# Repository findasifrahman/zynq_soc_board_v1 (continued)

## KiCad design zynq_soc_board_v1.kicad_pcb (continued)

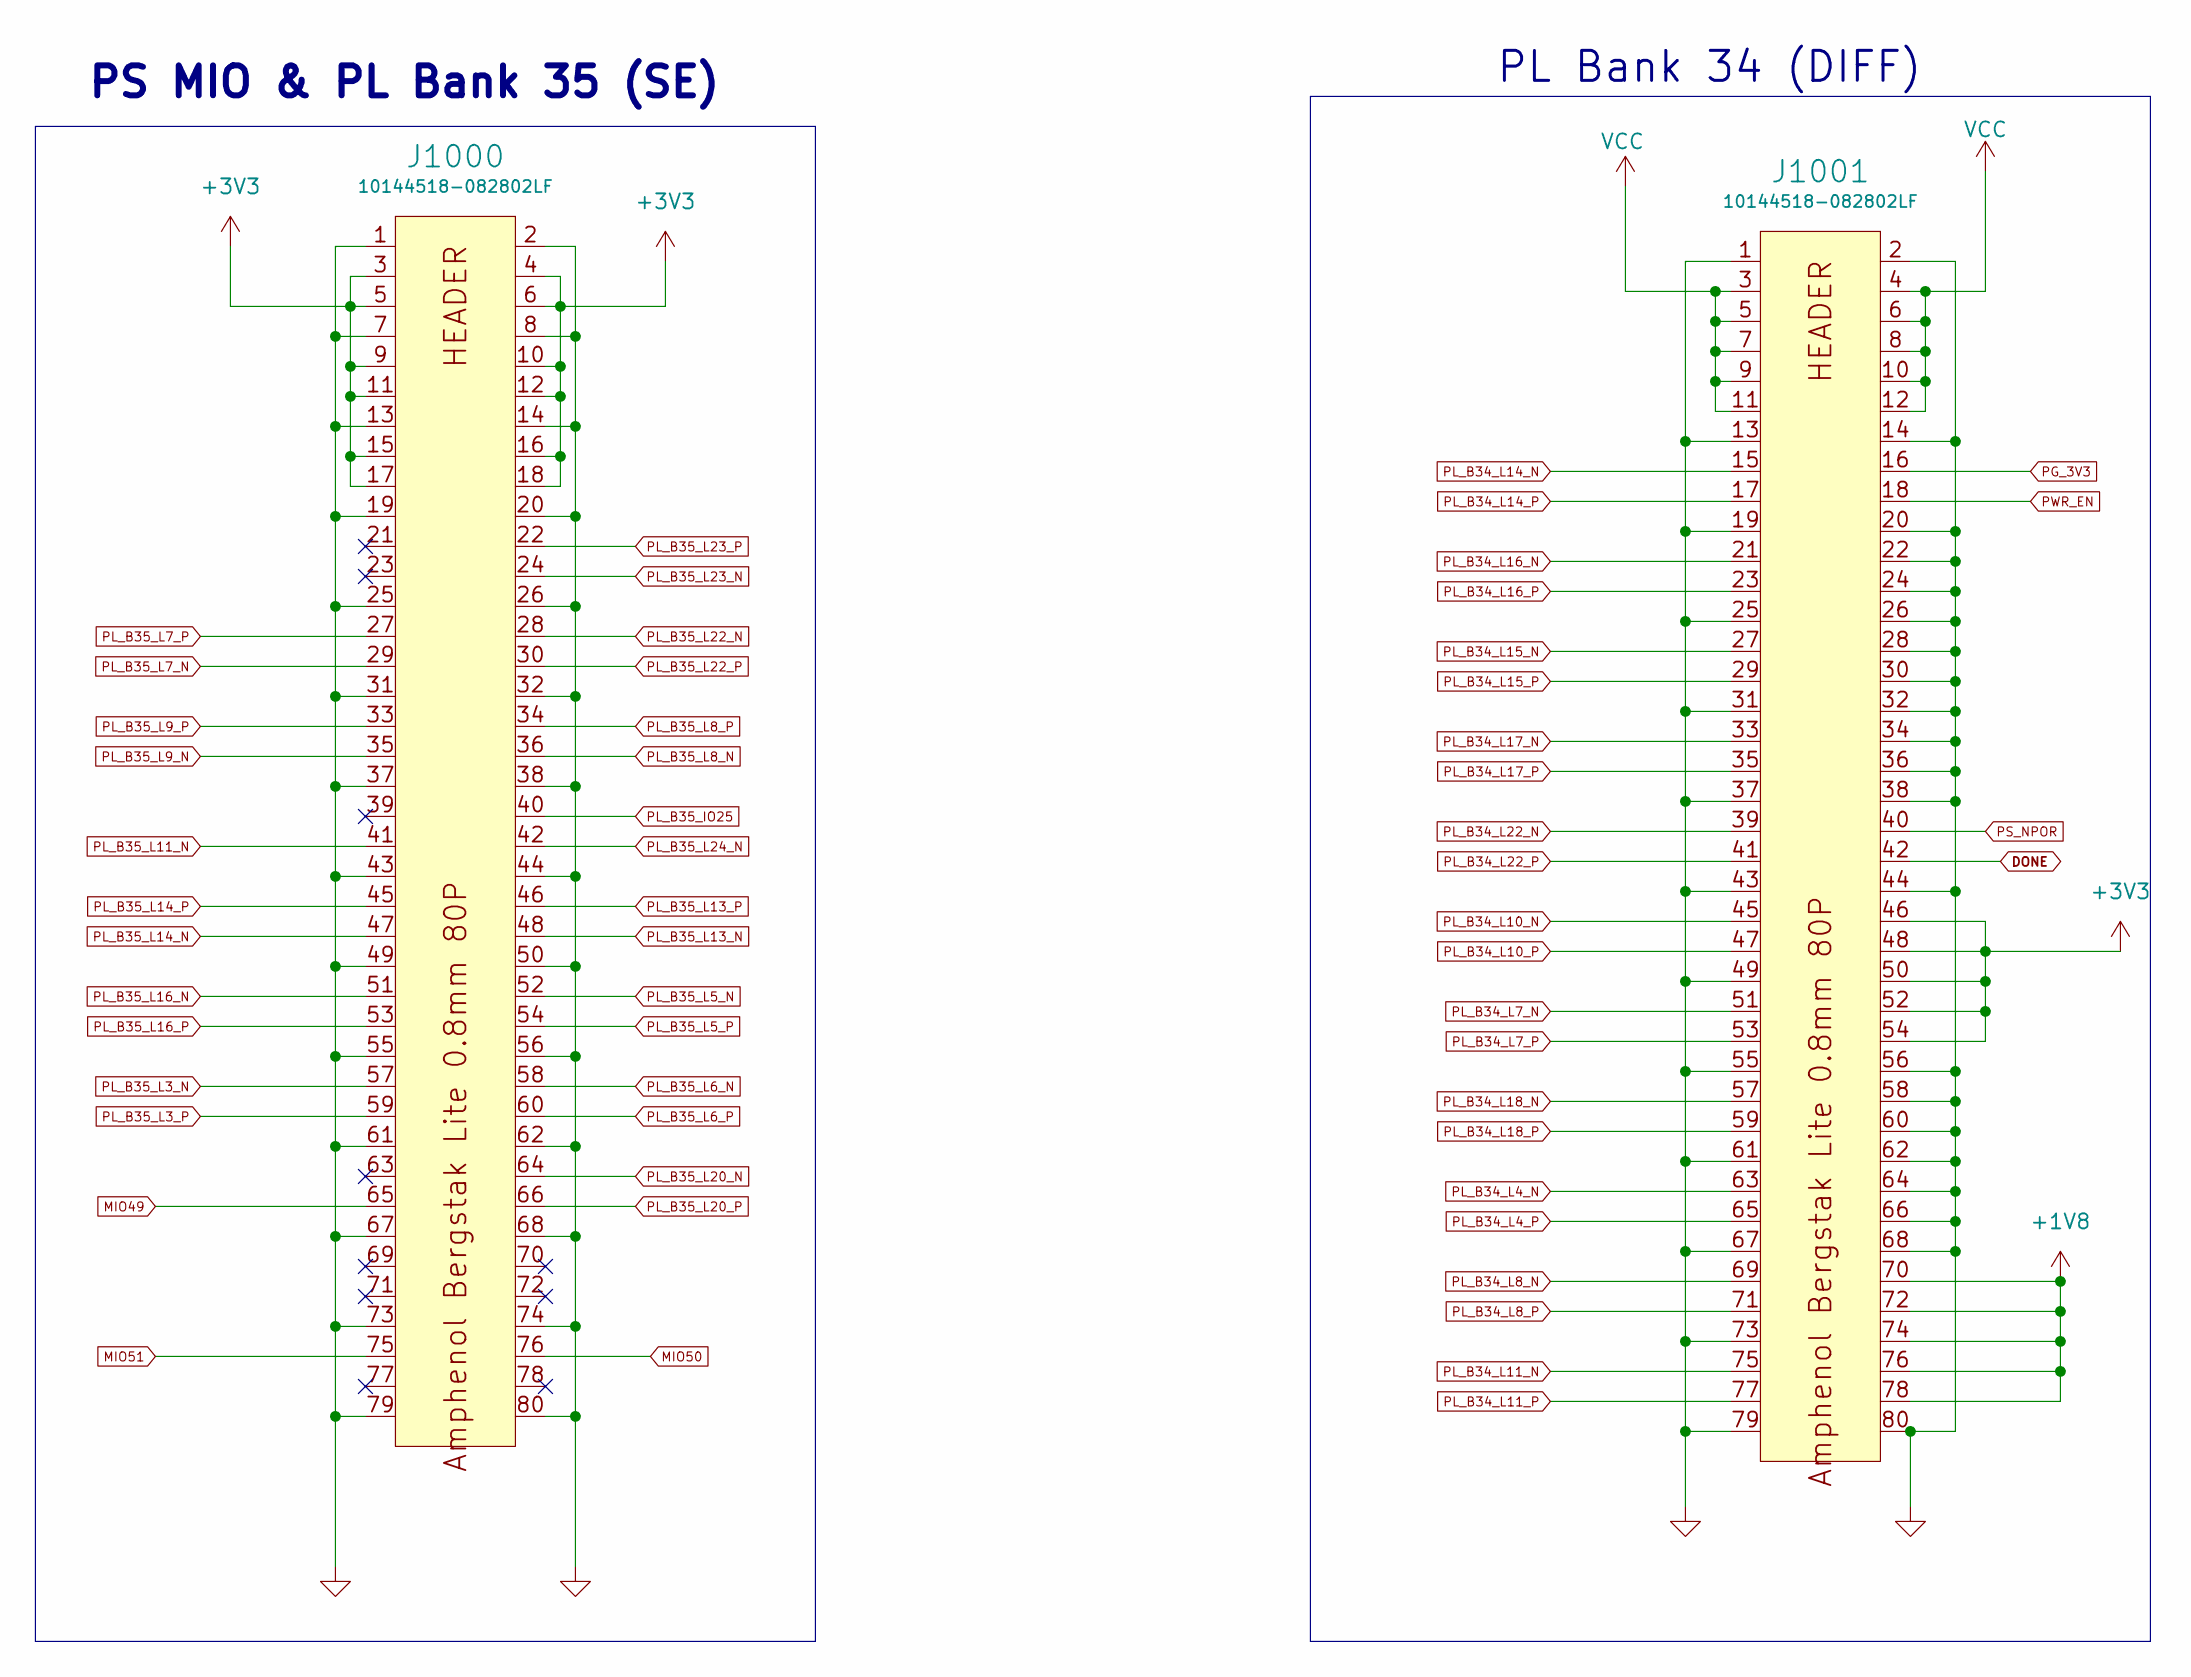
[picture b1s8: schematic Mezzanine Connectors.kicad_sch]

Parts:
J1000, J1001: 10144518-082802LF; Manufacturer Part Number 10144518-082802LF; LCSC C3653168

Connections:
+1V8: J1001.70, J1001.72, J1001.74, J1001.76, J1001.78; also elsewhere on the board
+3V3: J1000.3, J1000.4, J1000.5, J1000.6, J1000.9, J1000.10, J1000.11, J1000.12, J1000.15, J1000.16, J1000.17, J1000.18, J1001.46, J1001.48, J1001.50, J1001.52, J1001.54; also elsewhere on the board
DONE: J1001.42; also elsewhere on the board
GND: J1000.1, J1000.2, J1000.7, J1000.8, J1000.13, J1000.14, J1000.19, J1000.20, J1000.25, J1000.26, J1000.31, J1000.32, J1000.37, J1000.38, J1000.43, J1000.44, J1000.49, J1000.50, J1000.55, J1000.56, J1000.61, J1000.62, J1000.67, J1000.68, J1000.73, J1000.74, J1000.79, J1000.80, J1001.1, J1001.2, J1001.13, J1001.14, J1001.19, J1001.20, J1001.22, J1001.24, J1001.25, J1001.26, J1001.28, J1001.30, J1001.31, J1001.32, J1001.34, J1001.36, J1001.37, J1001.38, J1001.43, J1001.44, J1001.49, J1001.55, J1001.56, J1001.58, J1001.60, J1001.61, J1001.62, J1001.64, J1001.66, J1001.67, J1001.68, J1001.73, J1001.79, J1001.80; also elsewhere on the board
MIO49: J1000.65; also elsewhere on the board
MIO50: J1000.76; also elsewhere on the board
MIO51: J1000.75; also elsewhere on the board
PG_3V3: J1001.16; also elsewhere on the board
PL_B34_L4_N: J1001.63; also elsewhere on the board
PL_B34_L4_P: J1001.65; also elsewhere on the board
PL_B34_L7_N: J1001.51; also elsewhere on the board
PL_B34_L7_P: J1001.53; also elsewhere on the board
PL_B34_L8_N: J1001.69; also elsewhere on the board
PL_B34_L8_P: J1001.71; also elsewhere on the board
PL_B34_L10_N: J1001.45; also elsewhere on the board
PL_B34_L10_P: J1001.47; also elsewhere on the board
PL_B34_L11_N: J1001.75; also elsewhere on the board
PL_B34_L11_P: J1001.77; also elsewhere on the board
PL_B34_L14_N: J1001.15; also elsewhere on the board
PL_B34_L14_P: J1001.17; also elsewhere on the board
PL_B34_L15_N: J1001.27; also elsewhere on the board
PL_B34_L15_P: J1001.29; also elsewhere on the board
PL_B34_L16_N: J1001.21; also elsewhere on the board
PL_B34_L16_P: J1001.23; also elsewhere on the board
PL_B34_L17_N: J1001.33; also elsewhere on the board
PL_B34_L17_P: J1001.35; also elsewhere on the board
PL_B34_L18_N: J1001.57; also elsewhere on the board
PL_B34_L18_P: J1001.59; also elsewhere on the board
PL_B34_L22_N: J1001.39; also elsewhere on the board
PL_B34_L22_P: J1001.41; also elsewhere on the board
PL_B35_IO25: J1000.40; also elsewhere on the board
PL_B35_L3_N: J1000.57; also elsewhere on the board
PL_B35_L3_P: J1000.59; also elsewhere on the board
PL_B35_L5_N: J1000.52; also elsewhere on the board
PL_B35_L5_P: J1000.54; also elsewhere on the board
PL_B35_L6_N: J1000.58; also elsewhere on the board
PL_B35_L6_P: J1000.60; also elsewhere on the board
PL_B35_L7_N: J1000.29; also elsewhere on the board
PL_B35_L7_P: J1000.27; also elsewhere on the board
PL_B35_L8_N: J1000.36; also elsewhere on the board
PL_B35_L8_P: J1000.34; also elsewhere on the board
PL_B35_L9_N: J1000.35; also elsewhere on the board
PL_B35_L9_P: J1000.33; also elsewhere on the board
PL_B35_L11_N: J1000.41; also elsewhere on the board
PL_B35_L13_N: J1000.48; also elsewhere on the board
PL_B35_L13_P: J1000.46; also elsewhere on the board
PL_B35_L14_N: J1000.47; also elsewhere on the board
PL_B35_L14_P: J1000.45; also elsewhere on the board
PL_B35_L16_N: J1000.51; also elsewhere on the board
PL_B35_L16_P: J1000.53; also elsewhere on the board
PL_B35_L20_N: J1000.64; also elsewhere on the board
PL_B35_L20_P: J1000.66; also elsewhere on the board
PL_B35_L22_N: J1000.28; also elsewhere on the board
PL_B35_L22_P: J1000.30; also elsewhere on the board
PL_B35_L23_N: J1000.24; also elsewhere on the board
PL_B35_L23_P: J1000.22; also elsewhere on the board
PL_B35_L24_N: J1000.42; also elsewhere on the board
PS_NPOR: J1001.40; also elsewhere on the board
PWR_EN: J1001.18; also elsewhere on the board
VCC: J1001.3, J1001.4, J1001.5, J1001.6, J1001.7, J1001.8, J1001.9, J1001.10, J1001.11, J1001.12; also elsewhere on the board

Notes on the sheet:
PS MIO & PL Bank 35 (SE)
PL Bank 34 (DIFF)

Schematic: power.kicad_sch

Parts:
C100, C103, C104, C107, C108, C109, C112, C113, C114, C117, C118, C119, C122, C123, C124, C127: 22u; C0805; Manufacturer Part Number CL21A226MAQNNNE; LCSC C45783
C101, C102, C105, C110, C115: 100n; C_0402_1005Metric; Manufacturer Part Number CL05B104KO5NNNC; LCSC C1525
C106, C111, C116, C121: 22p; C_0402_1005Metric; Manufacturer Part Number 0402CG220J500NT; LCSC C1555
C120, C125, C126, C128, C129: 4u7; C_0402_1005Metric; Manufacturer Part Number CL05A475MP5NRNC; LCSC C23733
C130: 1nf,250v; C2211; Manufacturer Part Number GA352QR7GF102KW01L; LCSC C91599
D100: PMEG1030EJ; D_SOD-323F; LCSC C133633
D101: RED; LED_0402_RED; Manufacturer Part Number NCD0402R1; LCSC C130719
H1, H2, H3, H4: MountingHole; MountingHole_3.2mm_M3
J100: CON-SOCJ-2155; DC-IN-TH_DC005-T20; Manufacturer Part Number CON-SOCJ-2155; LCSC C111567
L100, L101, L102, L103: 2uh2; IND-SMD_L4.4-W4.1; Manufacturer Part Number SRP0415-2R2K; LCSC C1858073
Q100: T2N7002AK; SOT-23; Manufacturer Part Number T2N7002AK,LM; LCSC C516175
R100, R126: 100k; R_0402_1005Metric; Manufacturer Part Number 0402WGF1003TCE; LCSC C25741
R101, R103, R105, R108, R110, R113, R115, R118, R120, R123, R125: 12K; R_0402_1005Metric; Manufacturer Part Number 0402WGF1202TCE; LCSC C25752
R102: 4K7; R_0402_1005Metric; Manufacturer Part Number 0402WGF4701TCE; LCSC C25900
R104, R107, R109, R112, R114, R117, R119, R122: 100K; R_0402_1005Metric; Manufacturer Part Number 0402WGF1003TCE; LCSC C25741
R106: 68K; R_0402_1005Metric; Manufacturer Part Number 0603WAF6802T5E; LCSC C23231
R111: 200K; R_0402_1005Metric; Manufacturer Part Number 0402WGF2003TCE; LCSC C25764
R116: 124K; R_0402_1005Metric; Manufacturer Part Number 0402WGF1243TCE; LCSC C36777
R121: 453K; R_0402_1005Metric; Manufacturer Part Number 0402WGF4533TCE; LCSC C27009
R124: 510; R_0402_1005Metric; Manufacturer Part Number RC-02W511JT; LCSC C1119
R127: 1k; R_0402_1005Metric; Manufacturer Part Number 0402WGF1001TCE; LCSC C11702
R128: DNP_1M; R_0402_1005Metric
U100: LS1205EVD33; DFN3x3_10L; Manufacturer Part Number LS1205EVD33; LCSC C6653278
U101, U102, U103, U104: SY8003ADFC; DFN-8_L2.0-W2.0-P0.50-LS2.0-BL-EP; Manufacturer Part Number High Efficiency 5.5V, 3A continuous, 1M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; LCSC C178236
U105: BD3539FVM-TR; MSOP8; Manufacturer Part Number BD3539FVM-TR; LCSC C213437

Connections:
+0V675: C127.1, C128.1, U105.3 (VTTS), U105.8 (VTT); also elsewhere on the board
+0V675_REF: C129.1, U105.4 (VREF); also elsewhere on the board
+1V0: C106.1, C107.1, C108.1, L100.2, R106.2; also elsewhere on the board
+1V8: C111.1, C112.1, C113.1, L101.2, R111.2; also elsewhere on the board
+1V35: C116.1, C117.1, C118.1, L102.2, R116.2, R127.1; also elsewhere on the board
+3V3: C121.1, C122.1, C123.1, L103.2, R121.2; also elsewhere on the board
+5V: C103.1, C104.1, C109.1, C114.1, C119.1, C124.1, C126.1, R103.2, R105.1, R108.2, R113.2, R118.2, R124.2, U100.8 (OUT), U100.9 (OUT), U100.10 (OUT), U101.3 (IN), U102.3 (IN), U103.3 (IN), U104.3 (IN), U105.6 (VCC), U105.7 (VTT_IN)
+VDC: D100.2 (A), J100.1
/power/DDR_VTT_VDDQ: C125.1, R127.2, U105.5 (VDDQ)
/power/EFUSE_ILIM: R102.2, U100.5 (ILIM)
/power/EFUSE_VCP: R101.1, U100.4 (VCP)
/power/EN_1V0: R105.2, U101.7 (EN)
/power/EN_1V8: R110.2, U102.7 (EN)
/power/EN_1V35: R115.2, U103.7 (EN)
/power/EN_3V3: R120.2, U104.7 (EN)
/power/FB_1V0: C106.2, R106.1, R107.2, U101.1 (FB)
/power/FB_1V8: C111.2, R111.1, R112.2, U102.1 (FB)
/power/FB_1V35: C116.2, R116.1, R117.2, U103.1 (FB)
/power/FB_3V3: C121.2, R121.1, R122.2, U104.1 (FB)
/power/LED_PWR_A: D101.A, R124.1
/power/LED_PWR_K: D101.K, Q100.3 (D)
/power/SW_1V0: L100.1, U101.6 (LX)
/power/SW_1V8: L101.1, U102.6 (LX)
/power/SW_1V35: L102.1, U103.6 (LX)
/power/SW_3V3: L103.1, U104.6 (LX)
CGND: C130.1, R128.1; also elsewhere on the board
DDR_VTT_EN: R125.1, R126.1, U105.2 (EN)
EFUSE_SS: C102.1, U100.6 (SS)
GND: C100.2, C101.2, C102.2, C103.2, C104.2, C105.2, C107.2, C108.2, C109.2, C110.2, C112.2, C113.2, C114.2, C115.2, C117.2, C118.2, C119.2, C120.2, C122.2, C123.2, C124.2, C125.2, C126.2, C127.2, C128.2, C129.2, C130.2, J100.2, J100.3, Q100.2 (S), R102.1, R104.1, R107.1, R109.1, R112.1, R114.1, R117.1, R119.1, R122.1, R126.2, R128.2, U100.11 (GND), U101.4 (PGND), U101.8 (SGND), U101.9 (PGND), U102.4 (PGND), U102.8 (SGND), U102.9 (PGND), U103.4 (PGND), U103.8 (SGND), U103.9 (PGND), U104.4 (PGND), U104.8 (SGND), U104.9 (PGND), U105.1 (GND); also elsewhere on the board
unnamed: Q100.1 (G), R123.1
PG_1V0: C105.1, R103.1, R104.2, R110.1, U101.2 (PG)
PG_1V8: C110.1, R108.1, R109.2, R115.1, U102.2 (PG)
PG_1V35: C115.1, R113.1, R114.2, R120.1, R125.2, U103.2 (PG)
PG_3V3: C120.1, R118.1, R119.2, R123.2, U104.2 (PG); also elsewhere on the board
PWR_EN: C101.1, R100.2, U100.7 (EN); also elsewhere on the board
VCC: C100.1, D100.1 (K), R100.1, R101.2, U100.1 (IN), U100.2 (IN), U100.3 (IN); also elsewhere on the board

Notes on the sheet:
INPUT POWER & EFUSE
DDR3L VTT Regulator
BUCK CONVERTERS
CHASIS GND CONNECTION

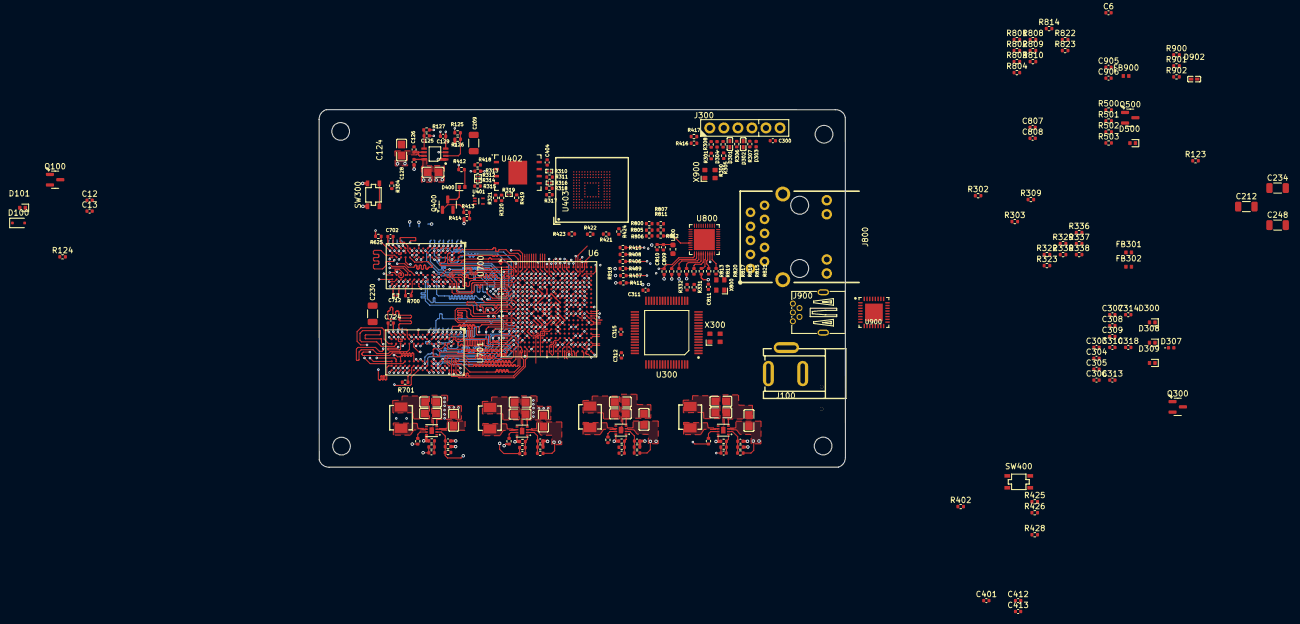
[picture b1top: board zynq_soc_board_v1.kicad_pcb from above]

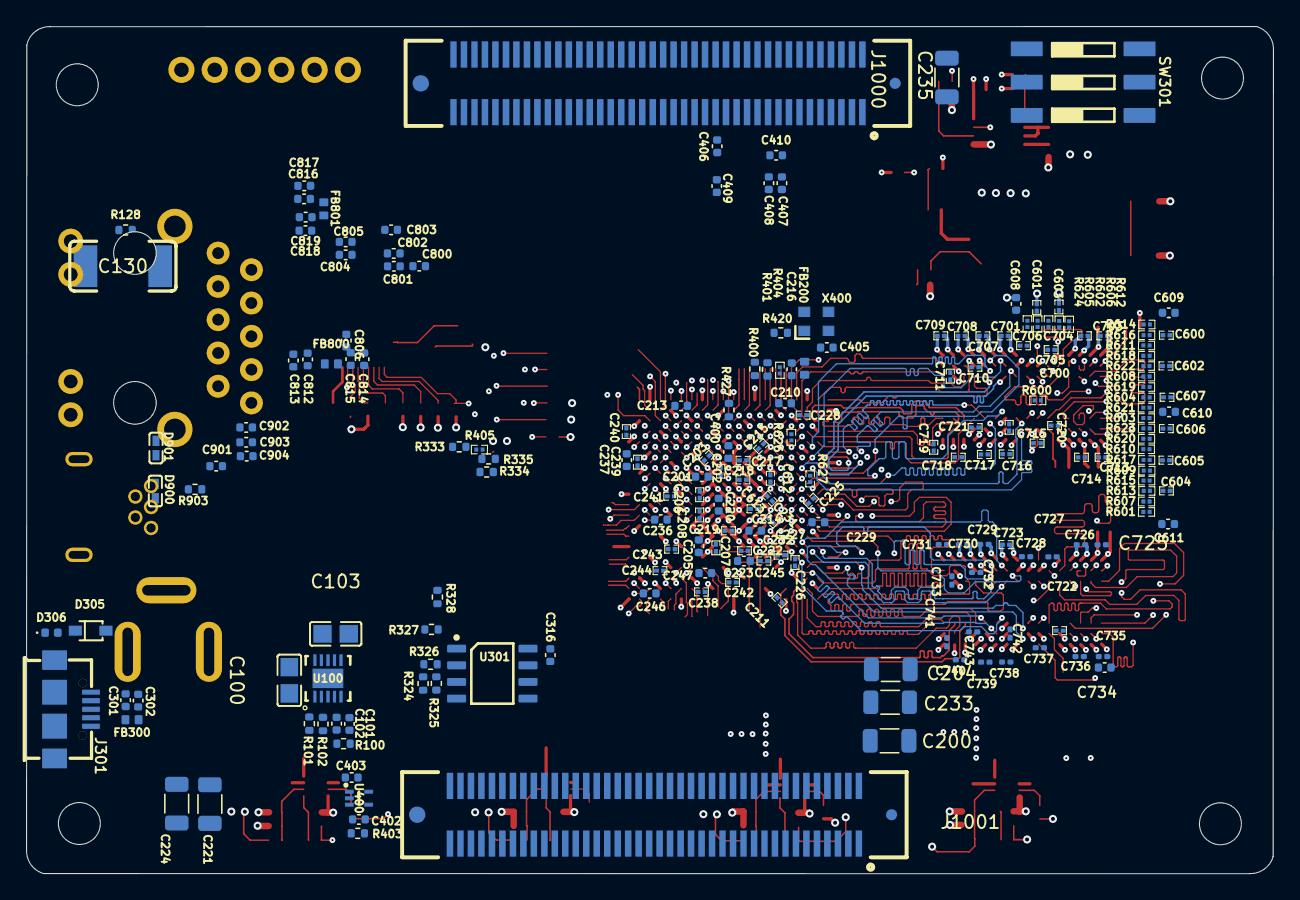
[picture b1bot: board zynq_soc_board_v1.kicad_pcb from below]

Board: 10 copper layers, 95.1 x 64.6 mm, 424 parts (198 on the bottom side), 316 nets.

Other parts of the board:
C12, C13: 47n; C_0402_1005Metric

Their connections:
+0V675_REF: C12.2, C13.1; also elsewhere on the board
+1V35: C12.1; also elsewhere on the board
GND: C13.2; also elsewhere on the board

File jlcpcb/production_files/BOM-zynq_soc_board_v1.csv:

Comment,Designator,Footprint,LCSC,Quantity
"1nf,250v",C130,C_1206_3216Metric,C107211,1
CON-SOCJ-2155,J100,DC-IN-TH_DC005-T20,C111567,1
510,"R124,R309,R336,R337,R412,R503,R822,R823,R905",R_0402_1005Metric,C1119,9
1k,"R127,R311,R313,R315,R318,R321,R500,R803,R805,R806,R813,R814,R900",R_0402_1005Metric,C11702,13
2u2,"C407,C409,C412",C_0402_1005Metric,C12530,3
RED,"D101,D300,D308,D309,D400,D500",LED_0402_RED,C130719,6
USB3320C-EZK-TR,U900,QFN-32_L5.0-W5.0-P0.50-BL-EP3.4,C132156,1
PMEG1030EJ,"D100,D305,D903",SOD-323_L1.8-W1.3-LS2.5-RD,C133633,3
100u,"C200,C204,C209,C212,C221,C224,C230,C233,C234,C235,C248",C_1206_3216Metric,C15008,11
100n,"C101,C102,C105,C110,C115,C300,C304,C306,C307,C308,C309,C310,C311,C312,C313,C314,C316,C318,C400,C401,C402,C403,C404,C405,C406,C408,C410,C413,C801,C802,C803,C804,C805,C806,C807,C808,C810,C811,C813,C814,C817,C818,C900,C901,C902,C903,C904",C_0402_1005Metric,C1525,47
22p,"C106,C111,C116,C121",C_0402_1005Metric,C1555,4
49R9,"R601,R602,R603,R604,R605,R606,R607,R608,R609,R610,R611,R612,R613,R614,R615,R616,R617,R618,R619,R620,R621,R622,R623,R624",R0201,C155744,24
3uh3,L800,L_0603_1608Metric,C162581,1
SY8003ADFC,"U101,U102,U103,U104",DFN-8_L2.0-W2.0-P0.50-LS2.0-BL-EP,C178236,4
Digilent HS2 Header,J300,DIGILENT_HS2,C178289,1
SN74LVC1G07DRLR,"U400,U401",SOT-553-5_L1.6-W1.2-P0.50-LS1.6-BL,C183013,2
93LC56BT-I/SN,U301,SOIC-8_L5.0-W4.0-P1.27-LS6.0-BL,C183620,1
RTL8211F-CG,U800,WQFN-40_L5.0-W5.0-P0.4-BL-EP,C187932,1
BD3539FVM-TR,U105,MSOP-8_L2.9-W2.8-P0.65-LS4.0-BL,C213437,1
68K,R106,R_0402_1005Metric,C23231,1
4u7,"C120,C125,C126,C128,C129,C201,C205,C210,C213,C216,C220,C223,C229,C232,C236,C237,C246,C247,C301,C302,C303,C305,C315,C608,C609,C610,C611,C702,C712,C724,C734,C800,C809,C812,C815,C816,C819,C905,C906,C907,C908",C_0402_1005Metric,C23733,41
22R,"R305,R306,R307,R308,R329,R330,R331,R332,R333,R334,R335,R338,R406,R407,R408,R409,R410,R411,R419,R420,R427,R807,R808,R809,R810,R811,R812,R815,R816,R817,R901",R_0402_1005Metric,C25092,31
240R,"R700,R701",R_0402_1005Metric,C25094,2
100k,"R100,R104,R107,R109,R112,R114,R117,R119,R122,R126,R414,R416,R501",R_0402_1005Metric,C25741,13
10k,"R421,R422,R423,R424,R425",R_0402_1005Metric,C25744,5
12K,"R101,R103,R105,R108,R110,R113,R115,R118,R120,R123,R125,R324,R326,R327,R328,R402,R413,R417,R418,R502,R903",R_0402_1005Metric,C25752,21
200K,R111,R_0402_1005Metric,C25764,1
2K49,"R325,R821",R_0402_1005Metric,C25884,2
4K7,"R102,R300,R301,R302,R303,R304,R403,R625,R800,R801,R804,R818,R819,R820,R904",R_0402_1005Metric,C25900,15
8K06,R902,R_0402_1005Metric,C25923,1
ECS-2520MV-130-BN,X900,XTAL_2520,C2613032,1
Varistor,"D301,D302,D303,D304,D306,D307,D900,D901,D902",C0402,C2655393,9
453K,R121,R_0402_1005Metric,C27009,1
FT2232HL-REEL,U300,LQFP-64_L10.0-W10.0-P0.50-LS12.0-TL,C27882,1
20K,"R310,R312,R314,R316,R319,R404,R405",R0201,C295787,7
219-3LPST,SW301,219-3LPST,C2961925,1
10144518-082802LF,"J1000,J1001",10144518-082802LF,C3653168,2
MT41K256M16TW-107 IT:P,"U700,U701",FBGA-96_L14.0-W8.0-R16-C6-P0.80-TL,C367428,2
124K,R116,R_0402_1005Metric,C36777,1
120R,"FB200,FB300,FB301,FB302,FB800,FB801,FB900",FB_0402,C38480,7
MTFC8GAKAJCN-4M_IT,U403,FBGA-153_L13.0-W11.5-P0.50_KLMAG1JETD-B041,C395384,1
W25Q128JVEIQ,U402,WSON-8_L6.0-W8.0-P1.27-BL-EP,C401662,1
ECS-2520MV-250,X800,XTAL_2520,C405463,1
ECS-2520MV-33.3,X400,XTAL_2520,C405468,1
12Mhz-TXC Corp,X300,XTAL_2520,C409301,1
USB-MICRO-B,J301,MICRO-USB-SMD_5P-P0.65-H-M_MICRO-USB-5P,C40942,1
22u,"C100,C103,C104,C107,C108,C109,C112,C113,C114,C117,C118,C119,C122,C123,C124,C127",C0805,C45783,16
SKRPANE010,"SW300,SW400",SKRPANE010,C470426,2
T2N7002AK,"Q100,Q300,Q400,Q500",SOT-23,C516175,4
U-M-M5DW-W-1,J900,MINI-USB-TH_U-M-M5DW-W-1,C530648,1
HR911130A,J800,HR911130A,C54408,1
XC7Z020-2CLG400I,U6,Xilinx_CLG400,C569043,1
MIC2099-1YMT-TR,U901,UDFN-6_L1.6-W1.6-P0.50-BL-EP1.2,C621527,1
LS1205EVD33,U100,TDFN-10_L3.0-W3.0-P0.50-BL-EP-2.3-1,C6653278,1
470n,"C202,C203,C206,C207,C208,C211,C214,C215,C217,C218,C219,C222,C225,C226,C227,C228,C231,C238,C239,C240,C241,C242,C243,C244,C245,C604,C605,C606,C607,C703,C713,C725,C735",C0201,C76591,33
100R,"R600,R626,R627",R0201,C77623,3
47n,"C600,C601,C602,C603,C612,C613,C700,C701,C704,C705,C706,C707,C708,C709,C710,C711,C714,C715,C716,C717,C718,C719,C720,C721,C722,C723,C726,C727,C728,C729,C730,C731,C732,C733,C736,C737,C738,C739,C740,C741,C742,C743",C0201,C88917,42
2uh2,L100,IND-SMD_L4.4-W4.1,,1
2uh2,L101,IND-SMD_L4.4-W4.1,,1
DNP_OR,R426,R_0402_1005Metric,,1
DNP_OR,R317,R_0402_1005Metric,,1
100k,R322,R_0402_1005Metric,,1
DNP_OR,R320,R_0402_1005Metric,,1
2uh2,L103,IND-SMD_L4.4-W4.1,,1
100k,R323,R_0402_1005Metric,,1
2uh2,L102,IND-SMD_L4.4-W4.1,,1
DNP_OR,R428,R_0402_1005Metric,,1
DNP_4K7,R802,R_0402_1005Metric,,1
12K,R400,R_0402_1005Metric,,1
12K,R401,R_0402_1005Metric,,1
DNP_1M,R128,C_1206_3216Metric,,1

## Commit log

2024-11-30 PDF ADDED
2024-12-01 sch-updated
2024-12-02 sch_zynq_update
2024-12-03 sch updated zynq ddr
2024-12-04 sch-eth-usb-updated
2024-12-05 all page
2024-12-06 sch-to-pcb
2024-12-08 xc7z020-fanout
2024-12-13 ram-update
2024-12-21 ram-zynq-updated
2024-12-26 ram_ended
2024-12-31 pcb_eth
2025-01-03 usb hs update
2025-01-08 pcb layers
2025-01-10 pcbb
2025-01-13 rev a done
2025-02-22 zynq_soc_complete_hdmi
